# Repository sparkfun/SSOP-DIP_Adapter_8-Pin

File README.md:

SSOP DIP Adapter 8-Pin
======================
[
*SparkFun SSOP8 to DIP Adapter (BOB-00497)*](https://www.sparkfun.com/products/497)

This pcb breaks out SSOP 8-pin devices to standard 0.1" headers.

Repository Contents
-------------------
* **/Hardware** - All Eagle design files (.brd, .sch)

License Information
-------------------
The hardware is released under [Creative Commons ShareAlike 4.0 International](https://creativecommons.org/licenses/by-sa/4.0/).

Distributed as-is; no warranty is given.

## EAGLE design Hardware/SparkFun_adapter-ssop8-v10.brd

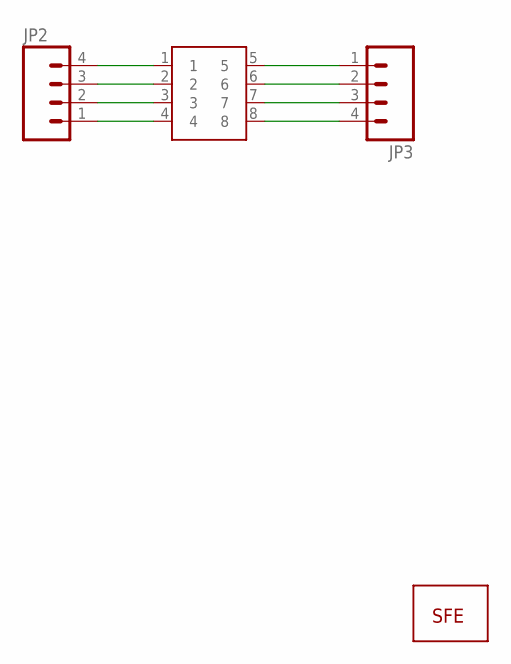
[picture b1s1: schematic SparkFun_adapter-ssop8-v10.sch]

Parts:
JP1: LOGO-SFESK; SFE-LOGO-FLAME
JP2, JP3: M04PTH; 1X04
U$1: SSOP8

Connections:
unnamed: JP2.1, U$1.4
unnamed: JP2.2, U$1.3
unnamed: JP2.3, U$1.2
unnamed: JP2.4, U$1.1
unnamed: JP3.1, U$1.5
unnamed: JP3.2, U$1.6
unnamed: JP3.3, U$1.7
unnamed: JP3.4, U$1.8

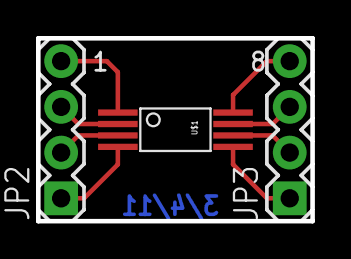
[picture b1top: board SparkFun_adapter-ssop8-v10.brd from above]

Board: 2 copper layers, 15.2 x 10.2 mm, 4 parts (1 on the bottom side), 8 nets.

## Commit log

2015-01-06 Initial hardware commit
